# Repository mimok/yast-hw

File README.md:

# Yet Another Security Token v1.0

## Purpose of this token
This repository contains the hardware source files of the YAST security token.
This security token is intented to be used as a development platform for security applications.
It is built around a LPC55Sxx chip and a SE050 secure element both from NXP.
This token as the same form factor as the [OpenSK](https://github.com/google/OpenSK) token
from Google therefore its [case](https://www.thingiverse.com/thing:4132768) can be reused.

## Disclaimer
YAST is designed to be a development board and therefore should not be used as a daily security token.

## What is the added value of YAST?
On the market there is already a large amount of security tokens.
Most of them are based on proprietary designs while some others are open source.
On one hand, closed source tokens seem to be based on secure elements while on the other hand, as far as I know, open source tokens
are based on standard, not security certified, chips like STM32 chips.
This design choice seems to be mainly dictated by concerns about NDA which come with Secure Elements.

From my point of view this is a real problem. I agree some tokens based on secure elements are not exempt from vulnerabilities like the 
[Titan security key](https://www.zdnet.com/article/new-side-channel-attack-can-recover-encryption-keys-from-google-titan-security-keys/) from Google.
In fact, this token is based on a pretty old secure element A7005 from NXP and therefore things which were secure almost ten years ago are no more secure now.
However if a old secure element is now vulnerable (but more than 4 months of work were needed to discover and exploit the vulnerability), 
old non secure chips are **far more** vulnerable. For example, it is possible to [extract the firmware](https://blog.zapb.de/stm32f1-exceptional-failure/) 
from an STM32F1 chip using a pure software attack (ok this is not entirely true as an access to the SWD port is needed). 
This is this chip which is used in the Nitrokey Start key from Nitrokey. While using a secure element is not a "cure-all", 
using non-secure and non-certified chips for secure application is almost always a bad idea as you relies on a "untrusted" 
(not certified) chip exectuting an "untrusted" (not certified) code. 
Here openness is not really a huge advantage as there is very few people around the world which have the required 
skills needed to perform a valuable security assessment of a security token.

So how a security token can be built using a secure element and still be open source? 
[SE050 security chip](https://www.nxp.com/products/security-and-authentication/authentication/edgelock-se050-plug-trust-secure-element-family-enhanced-iot-security-with-maximum-flexibility:SE050) 
from NXP is a pre-programmed secure element embedding a really versatile security applet. 
All documentation is freely accessible on NXP's website (some documentation requires an account to be accessible) and therefore no NDA is required. 
The YAST key embeds both a LPC55Sxx chip and the SE050 SE. LPC55Sxx chip can be binded to its SE050 companion using its embedded PUF (Physical Unclonable Function). 
The resulting hardware comes with both the flexibility and the power of the LPC55 chip and the security of the SE050 secure element which has been certified at level EAL6+ (Hardware and OS) according to the Common Criterias.

## For which application the YAST token can be used?
YAST token is made of a LPC55Sxx MCU connected to a SE050 coprocessor which acts as a secure cryptographic library.
SE050 is designed to prevent both leakage of cryptographic keys and their usage by unauthorized users. In consequence, YAST token is suited for
applications which extensively use cryptographic primitives. However, others processing taking place on the LPC55 side do not benefit from SE050 high
security level. So before using YAST token for a given application, you should be sure that the following hypothesis are verified:
- LPC55Sxx does not implements any security functions and it is only used as an interface between SE050 chip and the host PC.
- Or, LPC55Sxx implements some security function but they can only be used if the user is properly authenticated by the SE050 **and** , 
if we consider the application threat model,the user is not willing to attack his own token.

Concretely, the YAST token can be used to implement application like OpenPGP card (demo application available), 
FIDO2 protocol (but YAST token does not have any led) or HSM-like applications.

SE050 has some functional limitations which can be circumvented:

- PIN object cannot be atomically updated. You have to first delete then create a new PIN object. 
If a power loss occurs between PIN deletion and creation then the secure element remains in an improper state which can be exploited by an attacker. 
Therefore my advise is to lock the secure element using the new PIN before the deletion of the old PIN and unlock the SE at the end of the process. 
In case of power loss during PIN update, the SE is locked at next reboot and the improper state of the SE cannot be exploited by an attacker which does not have the knowledge of the new PIN.
- PIN try counters of PIN objects cannot be read (while there are effectively decremented when a wrong PIN is entered) 
so you will have to manage these counters by yourself. This limitation is corrected in the new version of the SE050 which is not yet available.

At the moment, due to a shortage in LPC55S69 chips, YAST token is based on a LPC55S28 chip which does not implement TrustZone.
However these two chips are PIN compatible and token design does not need to be changed if one wants to update the chip.

## Building the YAST token yourself
You can easily build this token yourself. The token is designed using Kicad v5 and you can inspect or modify its design.
You will need a PCB with a thickness of at least 2.0mm (best 2.4mm). You can also use a small piece of tape to improve the thickness of your PCB.
You should dispense paste on the PCB using a stencil. I use unleaded low temperature Chip Quik SMDLTLFP paste (melting point at 138°C).
Placement is not so hard because CMS are not smaller than 0603. The regulator, the SE050 and the LPC55 are the hardest parts to place.
Soldering is an easy game if you use a hot plate and a hot-air rework station.

## Programming and debugging
A 6-pin header is available for programming and debugging purpose through LPC55 SWD port. 
A low cost [LPC Link-2](https://www.nxp.com/design/microcontrollers-developer-resources/lpc-microcontroller-utilities/lpc-link2:OM13054)
from NXP can be used as a debugging probe. You should update it with the [segger firmware](https://www.segger.com/products/debug-probes/j-link/models/other-j-links/lpc-link-2/) to obtain the best performances.
USB port can also be used to program the LPC55 chip through the on-chip bootloader:

1. First you will have to enable the USB0 interface in the bootloader configuration. To do so, you can load and execute the following [piece of code](docs/unlock_USB0_bootloader.c) trough SWD interface.
2. Once bootloader has been unlocked, press the button on the token and plug it on your computer. Bootloader should be automatically detected on WIN10.
3. Then use [blhost](https://www.nxp.com/design/software/development-software/mcuxpresso-software-and-tools-/mcuboot-mcu-bootloader-for-nxp-microcontrollers:MCUBOOT) tool from NXP to flash your firmware:
    1. Compile your program using your preferred IDE (e.g. MCUXpresso) and generate an HEX file.
    2. Load the new HEX file using the following commands:

```bash
blhost -u 0x1FC9,0x21 -- flash-image <path_to_hex_file> erase 0
blhost -u 0x1FC9,0x21 -- reset
```

## Plastic case for YAST token
This token as the same form factor as the [OpenSK](https://github.com/google/OpenSK) token
from Google therefore its [case](https://www.thingiverse.com/thing:4132768) can be reused.
The case can be built using a 3D Printer and PLA plastic.

## License
This work is licensed under CC BY-SA 4.0

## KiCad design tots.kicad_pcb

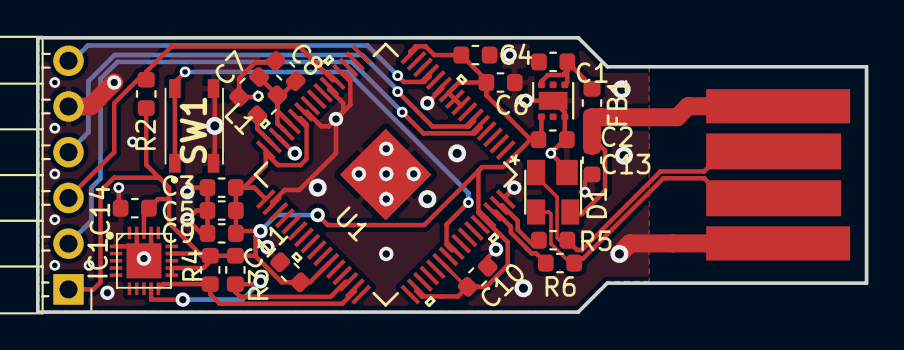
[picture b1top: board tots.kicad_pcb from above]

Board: 2 copper layers, 46.0 x 15.2 mm, 27 parts (0 on the bottom side), 17 nets.

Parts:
C1, C2: 1uF; C_0603_1608Metric
C3: 47pF; C_0603_1608Metric
C4, C5, C6, C8, C10, C11, C14: 100nF; C_0603_1608Metric
C7, C9: 10uF; C_0603_1608Metric
C13: 2.2uF; C_0603_1608Metric
D1: PRTR5V0U2X; SOT-143
FB1: 221R; L_0603_1608Metric
IC1: SE050C1HQ1_Z01SCZ; QFN40P300X300X33-21N-D
J2: Conn_01x06; PinHeader_1x06_P2.54mm_Horizontal
J3: USB HS; usb-PCB
L1: 4.7uH; L_0603_1608Metric
R2: 10k; R_0603_1608Metric
R3, R4: 560R; R_0603_1608Metric
R5, R6: 33R; R_0603_1608Metric
SW1: PTS810 SJK 250 SMTR LFS; PTS810SJG250SMTRLFS
U1: LPC55S28JBD64
U2: TLV75533PDRV; WSON-6-1EP_2x2mm_P0.65mm_EP1x1.6mm

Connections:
+3V3: C2.1, C3.1, C4.1, C5.1, C6.1, C9.1, C10.1, C11.1, C14.1, IC1.11, IC1.12, IC1.14, IC1.18, J2.1, R2.1, R3.1, R4.1, U1.8, U1.9, U1.10, U1.16, U1.27, U1.32, U1.33, U1.43, U1.50, U1.54, U1.61, U2.1
+5V: C1.1, FB1.1, U2.4, U2.6
/D+: D1.3, J3.3, R6.2
/D-: D1.2, J3.2, R5.2
/FC6_RXD: J2.4, U1.6
/FC6_SCK: J2.6, U1.13
/FC6_TXD: J2.2, U1.5
/ISP: SW1.1, SW1.2, U1.56
/RESET_N: J2.3, R2.2, U1.21
/VCC_USB: C13.1, D1.4, FB1.2, J3.1
GND: C1.2, C2.2, C3.2, C4.2, C5.2, C6.2, C7.1, C8.1, C9.2, C10.2, C11.2, C13.2, C14.2, D1.1, IC1.1, IC1.17, IC1.19, IC1.21, J2.5, J3.4, SW1.3, SW1.4, U1.11, U1.20, U1.22, U1.26, U1.30, U1.34, U1.64, U1.EPAD, U2.3, U2.7
unnamed: C7.2, C8.2, L1.2, U1.28, U1.29
unnamed: L1.1, U1.31
SE050_SCL: IC1.10, R4.2, U1.47
SE050_SDA: IC1.9, R3.2, U1.46
USB_N: R5.1, U1.63
USB_P: R6.1, U1.62

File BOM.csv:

Reference, Quantity, Value, Manufacturer_Name, Manufacturer_Part_Number
C1 C2 ,2,1uF,Taiyo Yuden ,EMK107BJ105KA-T 
C13 ,1,2.2uF,Taiyo Yuden,EMK107BJ225KA-T
C14 C11 C10 C6 C4 C5 C8 ,7,100nF,AVX,0603YC104MAT4A
C3 ,1,47pF,Wurth Elektronik,885012006021
C9 C7 ,2,10uF,Taiyo Yuden,EMK107BBJ106MA-T
D1 ,1,PRTR5V0U2X,Nexperia,"PRTR5V0U2X,215"
FB1 ,1,221R,Laird Performance Materials,MI0603L221R-10
IC1 ,1,SE050C1HQ1_Z01SCZ,Nexperia,SE050C1HQ1/Z01SCZ
L1 ,1,4.7uH,TDK,MLZ1608M4R7WT
R2 ,1,10k,Vishay,CRCW060310K0JNEBC
R3 R4 ,2,560R,Yageo,RC0603FR-07560RL
R5 R6 ,2,33R,Vishay,CRCW060333R0FKEAC
SW1 ,1,PTS810 SJK 250 SMTR LFS,C&K Switches,PTS810SJK250SMTRLFS
U1 ,1,LPC55S28JBD64,NXP,LPC55S28JBD64
U2 ,1,TLV75533PDRV,TI,TLV75533PDRV
,25,,,

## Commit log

2021-02-16 Update readme.md
    Readme updated with the project license
2021-02-16 Update README.md
    README updated
2021-02-17 Create LICENSE
2021-02-18 Documentation update
    Add a section about programming and debugging the YAST token.
    Add some illustration of the YAST token with and without its case.
2021-02-18 Documentation update
    Fix typos and reduce length of line in source file
2021-03-07 Documentation updated to highlight limitations of YAST token
    Actually YAST token cannot be used to implement any smartcard-like application.
    Indeed, any sensistive processing which would takes place on LPC55 side would be vulnerable to hardware attacks.
    The documentation is updated to highlight this limitation.

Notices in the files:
tots.kicad_pcb:
CC-BY-SA v4.0
CC-BY 4.0
parts and their libraries:
Copyright 2016 Accelerated Designs. All rights reserved.
